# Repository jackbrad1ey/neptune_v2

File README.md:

# Neptune V2

Neptune is a flight computer designed for testing basic thrust vector control (TVC) systems. It contains connectors for two servo motors with optional feedback, SWD and USB interfaces, radio communication using an RFM95W LoRa module and a 9-axis IMU for determining the attitude of the vehicle.

Neptune V2 aims to solve several issues identified in the first iteration, as well as improve upon the overall design. The noteable changes include:
- Improved connectors
  - JST-GH connectors for the servo motors to improve security and ease of connection
  - A more compact RF-antenna connector
- Indicator LEDs to display when the board has been powered on
- A more compact form factor
  - ~45% reduction in area
- A flash chip taking the place of an SD card connector
  - Improved reliability in high-vibration environments
- More suitable mounting holes
  - Clearance and strength issues were a problem in Neptune V1
- The addition of dedicated test points for easy debugging of basic issues

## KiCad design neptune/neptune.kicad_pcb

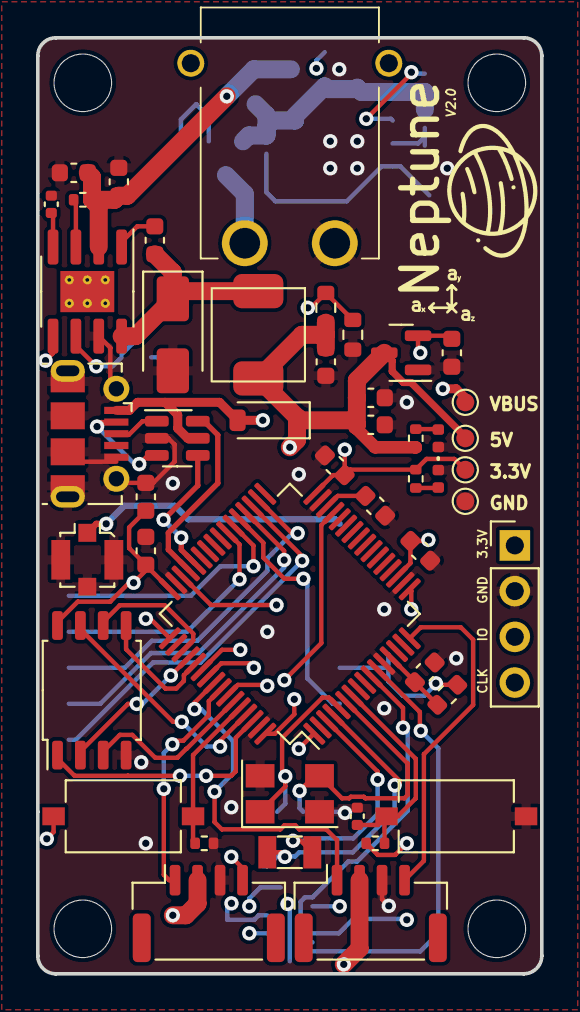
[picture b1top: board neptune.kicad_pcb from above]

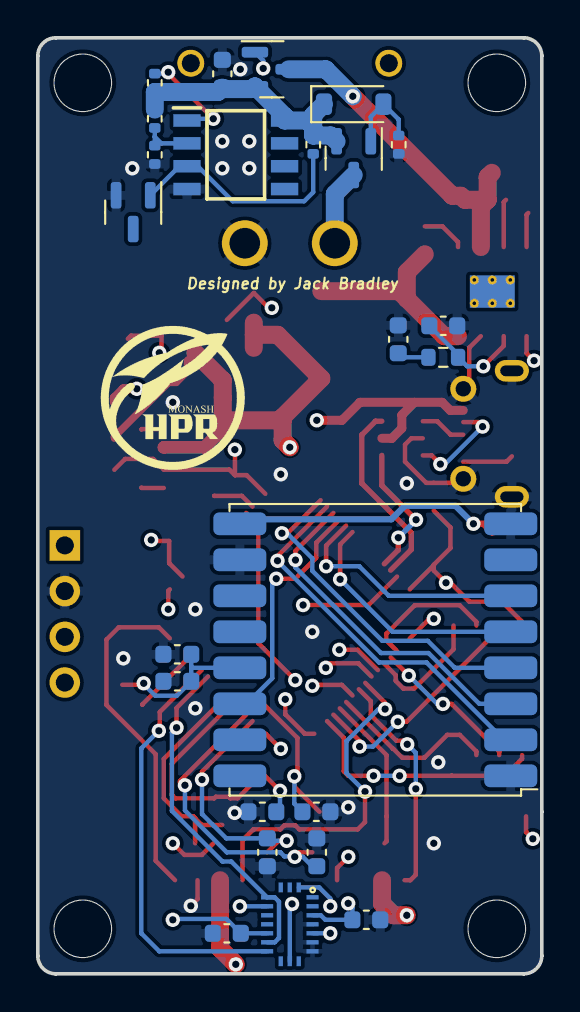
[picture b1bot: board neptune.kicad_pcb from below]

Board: 4 copper layers, 28.0 x 52.0 mm, 75 parts (24 on the bottom side), 57 nets.

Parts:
C1, C5, C8, C12, C13, C20, C21, C24, C25, C26: 100nF; C_0603_1608Metric
C2, C4, C11: 10u; C_0603_1608Metric
C3, C7, C22: 1u; C_0603_1608Metric
C6: 8.2n; C_0402_1005Metric
C9: 1n; C_0603_1608Metric
C10: 10p; C_0603_1608Metric
C14: 1u; C_0402_1005Metric
C15, C17: 33p; C_0603_1608Metric
C16, C18: 15p; C_0603_1608Metric
C19: 10n; C_0603_1608Metric
C23: 4.7u; C_0603_1608Metric
D1, D3: B5819W; D_SOD-123
D2: RB056LAM-40TR; D_SMA
D3#2, D5: LED; LED_0402_1005Metric
H1, H2, H3, H4: MountingHole; MountingHole_3.2mm_M3
J1: Conn_Coaxial; U.FL_Molex_MCRF_73412-0110_Vertical
J3: USB_B_Micro; USB_Micro-B_Molex-105017-0001
J4: Conn_01x02; XT30PWM
J5: Conn_01x04; PinHeader_1x04_P2.54mm_Vertical
J6, J7: Conn_01x04; JST_GH_SM04B-GHS-TB_1x04-1MP_P1.25mm_Horizontal
L1: IHLP2020CZER100M01
L2: 10u; L_0603_1608Metric
Q1: Si2301-TP; SOT-23
Q2: AO3401A; SOT-23
R1, R5: 100k; R_0402_1005Metric
R2, R4: 30k; R_0402_1005Metric
R3: 56k; R_0402_1005Metric
R6: NC; R_0402_1005Metric
R7: 36.5k; R_0603_1608Metric
R8: 10.2k; R_0603_1608Metric
R9: 1.91k; R_0603_1608Metric
R10, R11: 10k; R_0402_1005Metric
R10#2, R11#2: 200; R_0402_1005Metric
SW1, SW2: TS-1187A-B-A-B; SW_Tactile_SPST_NO_Straight_CK_PTS636Sx25SMTRLFS
TP1, TP2, TP3, TP4: TestPoint_Pad_D1.0mm
U1: ADR5040ARTZ-2.048; SOT-23
U2: LM393; SOIC127P600X175-8N
U3: TPS54331D; SOIC-8-1EP_3.9x4.9mm_P1.27mm_EP2.29x3mm_ThermalVias
U4: LP3993-33B3F; SOT-23
U5: RFM95W-915S2; HOPERF_RFM9XW_SMD
U6: STM32F411RETx; LQFP-64_10x10mm_P0.5mm
U7: BMX055
U8: USBLC6-2SC6; SOT-23-6
U10: AT25SF081-XMHF-X; SOP-8_5.28x5.23mm_P1.27mm
Y1: 12MHz; Crystal_SMD_5032-4Pin_5.0x3.2mm
Y2: 32.768k; Crystal_SMD_3215-2Pin_3.2x1.5mm

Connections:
+3V3: C7.1, C12.1, C13.1, C19.1, C20.1, C21.1, C22.1, C25.1, C26.1, J5.1, L2.1, R11.2, R11#2.1, SW1.2, TP4.1, U4.2 (VOUT), U5.13 (3.3V), U6.1 (VBAT), U6.19 (VDD), U6.32 (VDD), U6.48 (VDD), U6.64 (VDD), U7.3 (VDD), U7.13 (VDDIO), U10.8 (VCC)
+5V: C3.1, C5.1, C11.1, D3.1 (K), J6.2, J7.2, L1.2, R8.2, R10#2.1, TP2.1, U4.3 (VIN)
/Data management/CS_FC: U6.62 (PB9), U10.1 (~CS)
/Data management/CS_RF: U5.5 (NSS), U6.39 (PC8)
/Data management/HOLD_FC: U6.61 (PB8), U10.7 (~HOLD/IO3)
/Data management/MISO_FC: U6.52 (PC11), U10.2 (SO/IO1)
/Data management/MISO_RF: U5.2 (MISO), U6.35 (PB14)
/Data management/MOSI_FC: U6.53 (PC12), U10.5 (SI/IO0)
/Data management/MOSI_RF: U5.3 (MOSI), U6.36 (PB15)
/Data management/RESET_RF: U5.6 (RESET), U6.38 (PC7)
/Data management/RF_IO0: U5.14 (DIO0), U6.37 (PC6)
/Data management/SCK_FC: U6.51 (PC10), U10.6 (SCK)
/Data management/SCK_RF: U5.4 (SCK), U6.34 (PB13)
/Data management/WP_FC: U6.59 (PB7), U10.3 (~WP/IO2)
/Power/BATT: J4.1, Q1.3 (D)
/STM32/BOOT0: R10.2, SW1.1, U6.60 (BOOT0)
/STM32/CE_ACC: U6.58 (PB6), U7.16 (CSB1)
/STM32/CE_GYR: U6.55 (PB3), U7.5 (CSB2)
/STM32/CE_MAG: U6.54 (PD2), U7.20 (CSB3)
/STM32/IMU_MISO: U6.10 (PC2), U7.12 (SDO2), U7.17 (SDO1)
/STM32/IMU_MOSI: U6.11 (PC3), U7.11 (SDX)
/STM32/IMU_SCK: U6.29 (PB10), U7.9 (SCX)
/STM32/NRST: C14.1, R11.1, SW2.2, U6.7 (NRST)
/STM32/OSC32_IN: C16.1, U6.3 (PC14), Y2.1
/STM32/OSC32_OUT: C18.1, U6.4 (PC15), Y2.2
/STM32/OSC_IN: C15.1, U6.5 (PH0), Y1.1
/STM32/OSC_OUT: C17.1, U6.6 (PH1), Y1.3
/STM32/S1_control: J6.1, U6.56 (PB4)
/STM32/S1_feedback: J6.4, U6.16 (PA2)
/STM32/S2_control: J7.1, U6.57 (PB5)
/STM32/S2_feedback: J7.4, U6.17 (PA3)
/STM32/SWCLK: J5.4, U6.49 (PA14)
/STM32/SWDIO: J5.3, U6.46 (PA13)
/STM32/USB_D+: U6.45 (PA12), U8.6 (I/O1)
/STM32/USB_D-: U6.44 (PA11), U8.4 (I/O2)
GND: C1.2, C2.2, C3.2, C4.2, C5.2, C6.2, C7.2, C9.2, C10.2, C11.2, C12.2, C13.2, C14.2, C15.2, C16.2, C17.2, C18.2, C19.2, C20.2, C21.2, C22.2, C23.2, C24.2, C25.2, C26.2, D2.2 (A), D3#2.1 (K), D5.1 (K), J1.2 (Ext), J3.5 (GND), J3.6 (Shield), J4.2, J5.2, J6.3, J7.3, R1.1, R4.1, R9.1, R10.1, SW2.1, TP3.1, U1.2 (A), U2.4 (V-), U3.7 (GND), U4.1 (GND), U5.1 (GND), U5.8 (GND), U5.10 (GND), U6.12 (VSSA), U6.18 (VSS), U6.31 (VSS), U6.47 (VSS), U6.63 (VSS), U7.4 (GNDA), U7.6 (GNDIO), U7.7 (PS), U8.2 (GND), U10.4 (GND), Y1.2, Y1.4
unnamed: C9.1, R7.1
unnamed: D1.2 (A), Q1.1 (G), R1.2
unnamed: C8.2, D2.1 (K), L1.1, U3.8 (PH)
unnamed: D3#2.2 (A), R10#2.2
unnamed: D5.2 (A), R11#2.2
unnamed: J1.1 (In), U5.9 (ANT)
unnamed: J3.3 (D+), U8.1 (I/O1)
unnamed: J3.2 (D-), U8.3 (I/O2)
unnamed: Q2.1 (G), R5.1, U2.1
unnamed: R2.1, U1.1 (K), U2.3 (+)
unnamed: R3.1, R4.2, U2.2 (-)
unnamed: C8.1, U3.1 (BOOT)
unnamed: C10.1, R7.2, U3.6 (COMP)
unnamed: R6.1, U3.3 (EN)
unnamed: C6.1, U3.4 (SS)
unnamed: R8.1, R9.2, U3.5 (VSENSE)
unnamed: C23.1, U6.30 (VCAP1)
unnamed: C24.1, L2.2, U6.13 (VDDA)
VBUS: D3.2 (A), J3.1 (VBUS), TP1.1, U8.5 (VBUS)
VCC: C2.1, C4.1, Q2.3 (D), R6.2, U3.2 (VIN)
VDC: C1.1, D1.1 (K), Q1.2 (S), Q2.2 (S), R2.2, R3.2, R5.2, U2.8 (V+)

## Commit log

2023-06-30 Modified schematic, started routing
2023-06-30 Updated some footprints, restarted routing
2023-06-30 Continued routing
2023-06-30 Routed 3.3V stepdown, added indicator LEDs
2023-06-30 Finished routing
2023-06-30 Moved USB slightly, added 3D models
2023-06-30 Create LICENSE
2023-06-30 Small change
2023-07-01 Added images to .github
2023-07-01 Trimmed images slightly
2023-07-01 Fixed typo
